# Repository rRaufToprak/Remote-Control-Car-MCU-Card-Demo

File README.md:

# Remote-Control-Land-Vehicle-MCU-Card-Demo
# Demo software and firmware for the project are under development.

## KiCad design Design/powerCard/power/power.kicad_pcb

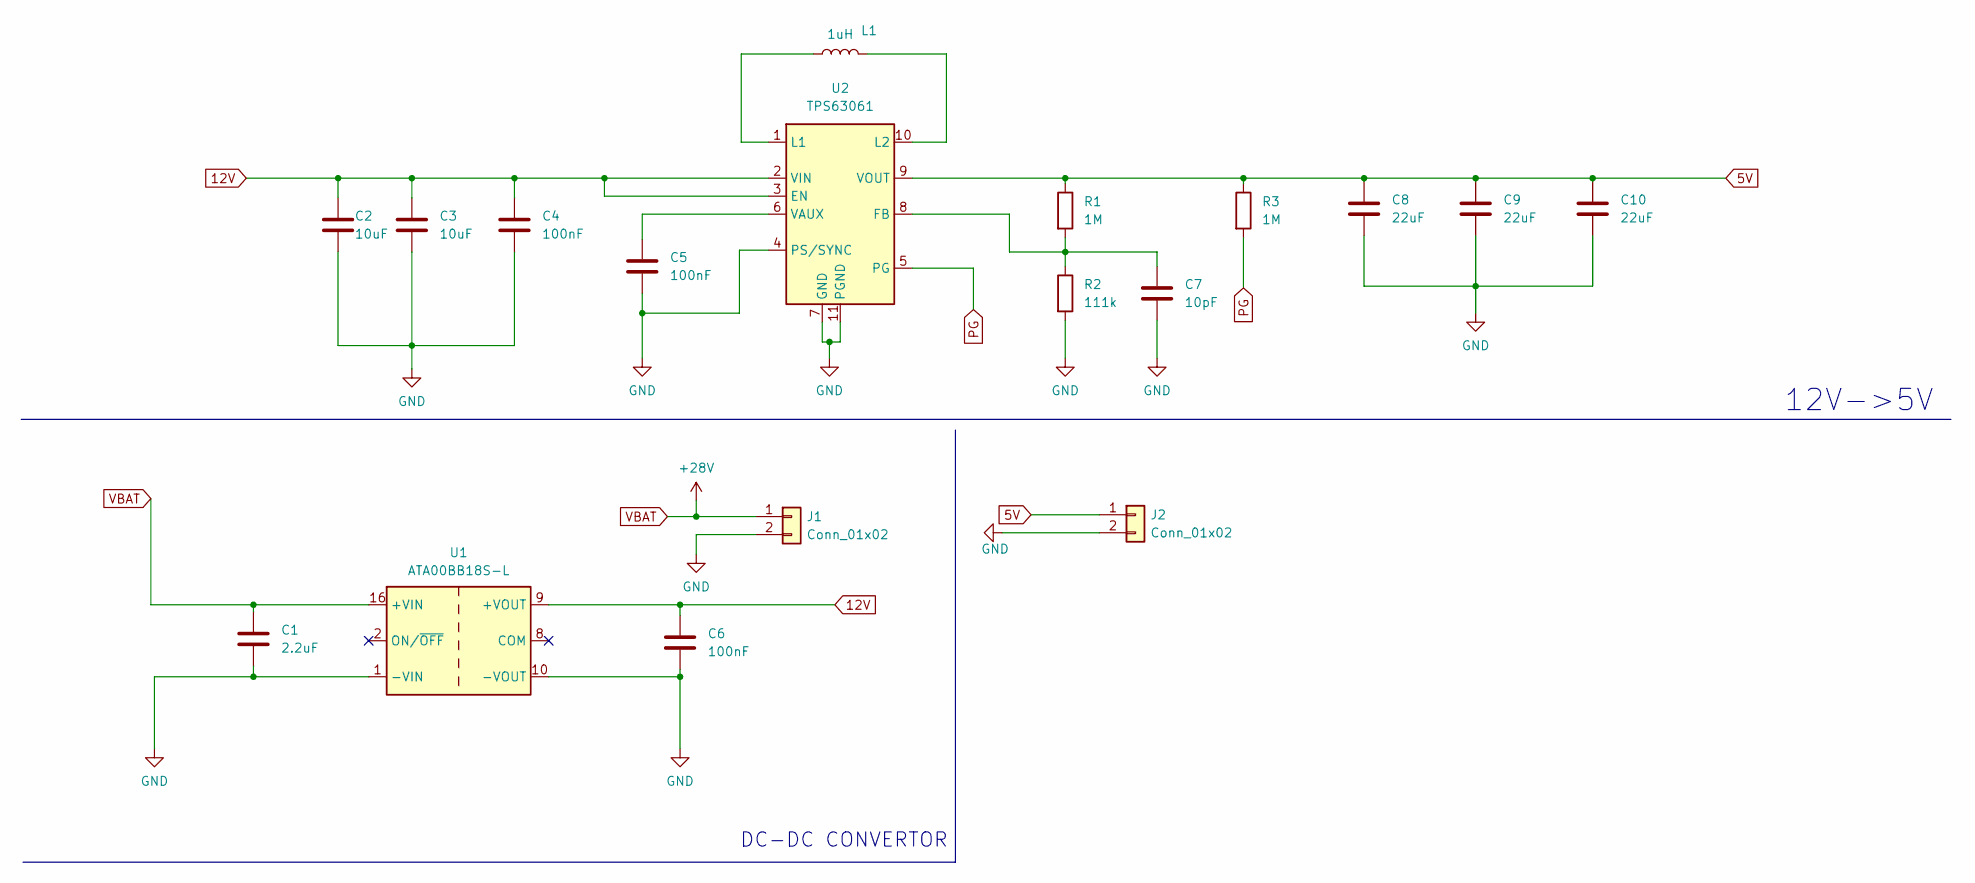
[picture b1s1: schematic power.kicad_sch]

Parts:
C1: 2.2uF; C_1206_3216Metric
C2, C3: 10uF; C_0805_2012Metric
C4, C5: 100nF; C_0805_2012Metric
C6: 100nF; C_1206_3216Metric
C7: 10pF; C_0805_2012Metric
C8, C9, C10: 22uF; C_0805_2012Metric
J1, J2: Conn_01x02; PinSocket_1x02_P2.54mm_Vertical
L1: 1uH; L_Wuerth_MAPI-3010
R1, R3: 1M; R_0805_2012Metric
R2: 111k; R_0805_2012Metric
U1: ATA00BB18S-L; Converter_DCDC_Artesyn_ATA_SMD
U2: TPS63061; Texas_S-PWSON-N10_ThermalVias

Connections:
5V: C8.1, C9.1, C10.1, J2.1, R1.1, R3.1, U2.9 (VOUT)
12V: C2.1, C3.1, C4.1, C6.1, U1.9 (+VOUT), U2.2 (VIN), U2.3 (EN)
GND: C1.2, C2.2, C3.2, C4.2, C5.2, C6.2, C7.2, C8.2, C9.2, C10.2, J1.2, J2.2, R2.2, U1.1 (-VIN), U1.10 (-VOUT), U2.4 (PS/SYNC), U2.7 (GND), U2.11 (PGND)
unnamed: C5.1, U2.6 (VAUX)
unnamed: C7.1, R1.2, R2.1, U2.8 (FB)
unnamed: L1.1, U2.1 (L1)
unnamed: L1.2, U2.10 (L2)
PG: R3.2, U2.5 (PG)
VBAT: C1.1, J1.1, U1.16 (+VIN)

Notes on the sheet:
12V->5V
DC-DC CONVERTOR

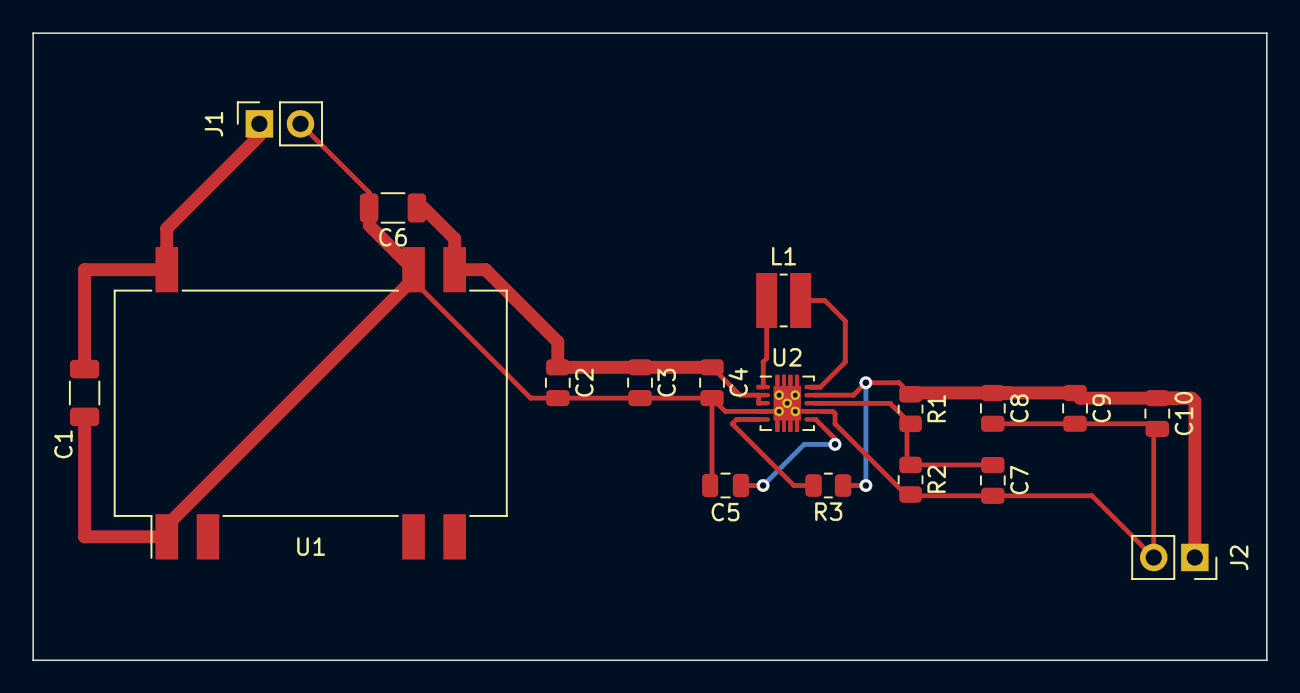
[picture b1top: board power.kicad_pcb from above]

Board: 2 copper layers, 76.2 x 38.7 mm, 18 parts (0 on the bottom side), 9 nets.

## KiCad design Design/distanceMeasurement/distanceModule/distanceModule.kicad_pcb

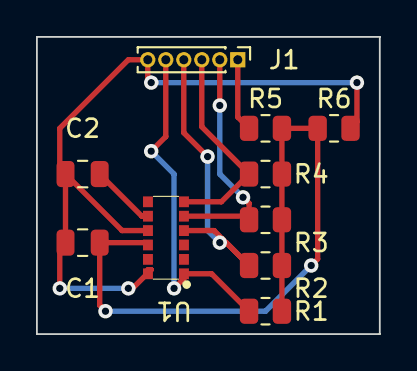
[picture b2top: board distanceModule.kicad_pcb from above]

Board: 2 copper layers, 19.0 x 16.5 mm, 10 parts (0 on the bottom side), 8 nets.

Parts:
C1: 100nF; C_0805_2012Metric
C2: 4.7uF; C_0805_2012Metric
J1: Header 1x6; PinHeader_1x06_P1.00mm_Vertical
R1, R2: 47k; R_0805_2012Metric
R3, R4: 10k; R_0805_2012Metric
R5: 5k; R_0805_2012Metric
R6: 28k; R_0805_2012Metric
U1: VL6180; vl6180

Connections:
2.8V: C1.1, R1.1, R2.1, R3.1, R4.1, R5.2, R6.1, U1.10 (AVDD)
3V3: J1.1, R5.1
GND: C1.2, C2.2, J1.6, R6.2, U1.9 (AVSS_VCSEL), U1.12 (GND)
GPIO0: J1.4, R2.2, U1.4 (IO0)
GPIO1: J1.5, R1.2, U1.1 (IO1)
unnamed: C2.1, U1.8 (AVDD_VCSEL)
SCL: J1.3, R4.2, U1.6 (SDA)
SDA: J1.2, R3.2, U1.5 (SCL)

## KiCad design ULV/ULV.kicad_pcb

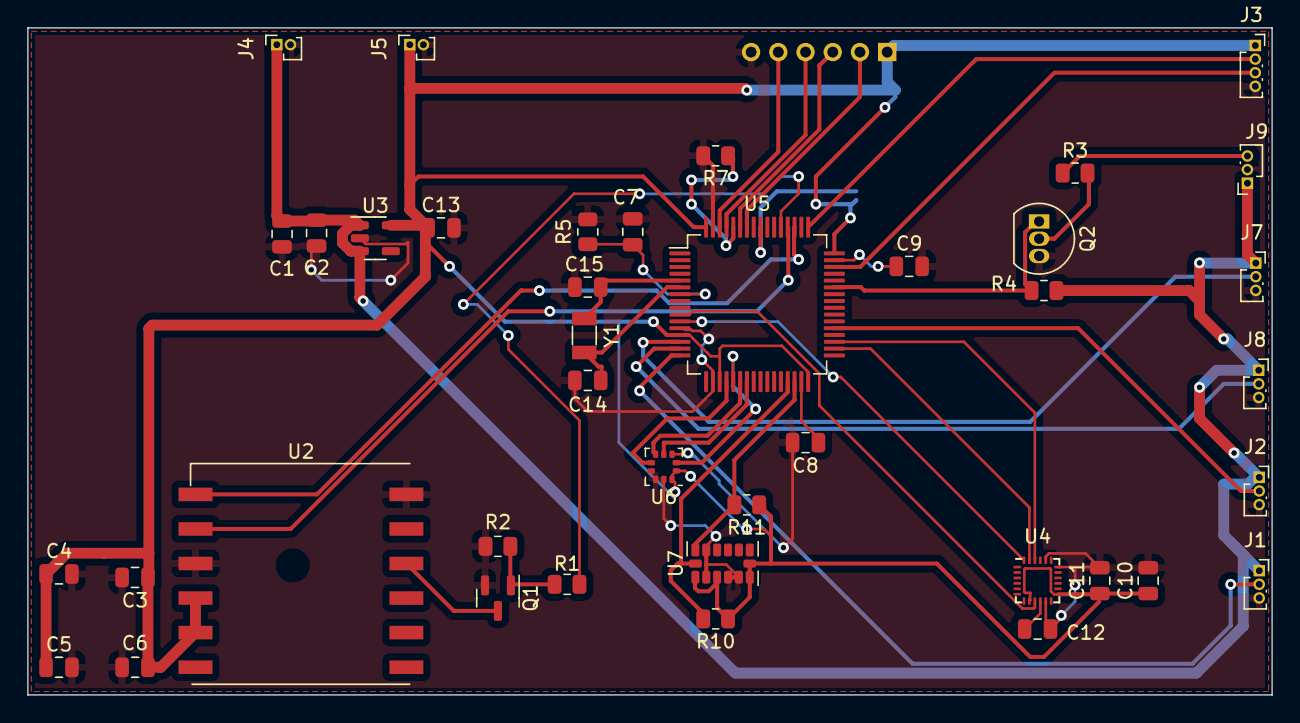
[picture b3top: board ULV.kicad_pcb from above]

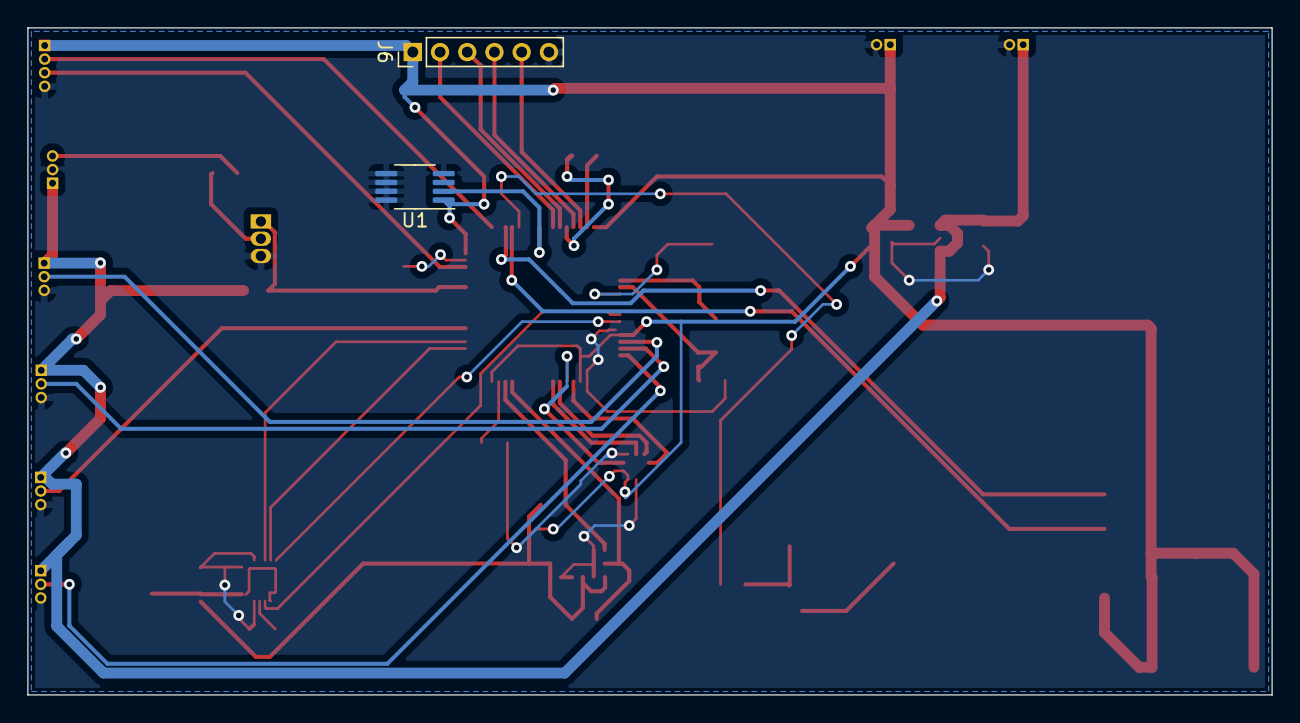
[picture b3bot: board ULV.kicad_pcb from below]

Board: 2 copper layers, 91.4 x 49.0 mm, 42 parts (2 on the bottom side), 39 nets.

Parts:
C1, C5: 1uF; C_0805_2012Metric
C2, C3, C4, C7, C10, C11, C12, C13: 100nF; C_0805_2012Metric
C6, C8, C9: 4.7uF; C_0805_2012Metric
C14, C15: 20pf; C_0805_2012Metric
J1, J2, J7, J8, J9: Conn_01x03; PinSocket_1x03_P1.00mm_Vertical
J3: Conn_01x04; PinSocket_1x04_P1.00mm_Vertical
J4, J5: Conn_01x02; PinSocket_1x02_P1.00mm_Vertical
J6: Conn_01x06; PinHeader_1x06_P2.00mm_Vertical
Q1: MMBT5551L; SOT-23
Q2: BC337; TO-92_Inline
R1, R4: 4.7k; R_0805_2012Metric
R2: 47k; R_0805_2012Metric
R3, R10, R11: 10k; R_0805_2012Metric
R5, R7: 100R; R_0805_2012Metric
U1: DS1825; MSOP-8_3x3mm_P0.65mm
U2: L80-R; Quectel_L80-R
U3: TLV70233_SOT23-5; SOT-23-5
U4: ICM-20948; InvenSense_QFN-24_3x3mm_P0.4mm
U5: STM32F405RGTx; LQFP-64_10x10mm_P0.5mm
U6: LPS25HB; ST_HLGA-10_2.5x2.5mm_P0.6mm_LayoutBorder3x2y
U7: ADXL343; LGA-14_3x5mm_P0.8mm_LayoutBorder1x6y
Y1: Crystal; Crystal_SMD_3215-2Pin_3.2x1.5mm

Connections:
3V3: C3.1, C4.1, C5.1, C6.1, C10.1, C11.1, C13.1, J3.1, J5.1, J6.1, R10.1, R11.1, U1.1 (VDD), U2.4 (VCC), U2.5 (V_BCKP), U3.5 (OUT), U4.8 (VDDIO), U4.13 (VDD), U5.13 (VDDA), U5.19 (VDD), U5.32 (VDD), U5.48 (VDD), U5.64 (VDD), U6.1 (VDDio), U6.10 (VDD), U7.1 (Vdd_I/O), U7.3 (RES), U7.6 (Vs), U7.7 (~CS)
5V: C1.1, C2.1, J1.1, J2.1, J4.1, J7.1, J8.1, J9.1, R4.1, U3.1 (IN), U3.3 (EN)
A_SCL: R10.2, U5.29 (PB10), U7.14 (SCL/SCLK)
A_SDA: R11.2, U5.30 (PB11), U7.13 (SDA/SDI/SDIO)
ESC_PWM1: J2.2, U5.37 (PC6)
ESC_PWM2: J7.2, U5.14 (PA0)
ESC_PWM3: J8.2, U5.15 (PA1)
ESC_PWM4: J1.2, U5.16 (PA2)
GND: C1.2, C2.2, C3.2, C4.2, C5.2, C6.2, C7.2, C8.2, C9.2, C10.2, C11.2, C12.2, C13.2, C14.1, C15.1, J1.3, J2.3, J3.4, J4.2, J5.2, J6.6, J7.3, J8.3, J9.2, Q1.2 (E), Q2.3 (E), R2.2, R5.1, R7.2, U1.4 (GND), U1.5 (AD0), U1.6 (AD1), U1.7 (AD2), U1.8 (AD3), U2.3 (GND), U2.12 (GND), U3.2 (GND), U4.11 (FSYNC), U4.18 (GND), U4.20 (GND), U5.12 (VSSA), U5.18 (VSS), U5.63 (VSS), U6.3 (GND), U6.7 (INT_DRDY), U6.8 (GND), U6.9 (GND), U7.2 (GND), U7.4 (GND), U7.5 (GND), U7.12 (SDO/ADDR)
GPS_RESET: R1.1, U5.53 (PC12)
GPS_RX: U2.1 (RXD1), U5.51 (PC10)
GPS_TX: U2.2 (TXD1), U5.52 (PC11)
G_MISO: U4.9 (SDO/AD0), U5.10 (PC2)
G_MOSI: U4.24 (SDA/SDI), U5.11 (PC3)
G_NSS: U4.22 (~CS), U5.35 (PB14)
G_SCLK: U4.23 (SCL/SCLK), U5.34 (PB13)
M_IO0_2: J6.4, U5.61 (PB8)
M_IO1_2: J6.5, U5.62 (PB9)
M_SCL_2: J6.2, U5.58 (PB6)
M_SDA_2: J6.3, U5.59 (PB7)
unnamed: C7.1, R5.2, U5.7 (NRST)
unnamed: C8.1, U5.31 (VCAP_1)
unnamed: C9.1, U5.47 (VCAP_2)
unnamed: C12.1, U4.10 (REGOUT)
unnamed: Q1.1 (B), R1.2, R2.1
unnamed: Q1.3 (C), U2.10 (~RESET)
unnamed: Q2.2 (B), R3.2
unnamed: R7.1, U5.60 (BOOT0)
OSC_IN: C15.2, U5.5 (PH0), Y1.2
OSC_OUT: C14.2, U5.6 (PH1), Y1.1
P_CS: U5.20 (PA4), U6.6 (~CS)
P_MISO: U5.22 (PA6), U6.5 (SA0/MISO)
P_MOSI: U5.23 (PA7), U6.4 (SDA/MOSI)
P_SCLK: U5.21 (PA5), U6.2 (SCL/SCLK)
SBUS_RX: Q2.1 (C), R4.2, U5.43 (PA10)
SBUS_SIGNAL: J9.3, R3.1
SWCLK: J3.2, U5.49 (PA14)
SWDIO: J3.3, U5.46 (PA13)
TEMP_W: U1.2 (DQ), U5.56 (PB4)

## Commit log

2023-10-15 README.md
